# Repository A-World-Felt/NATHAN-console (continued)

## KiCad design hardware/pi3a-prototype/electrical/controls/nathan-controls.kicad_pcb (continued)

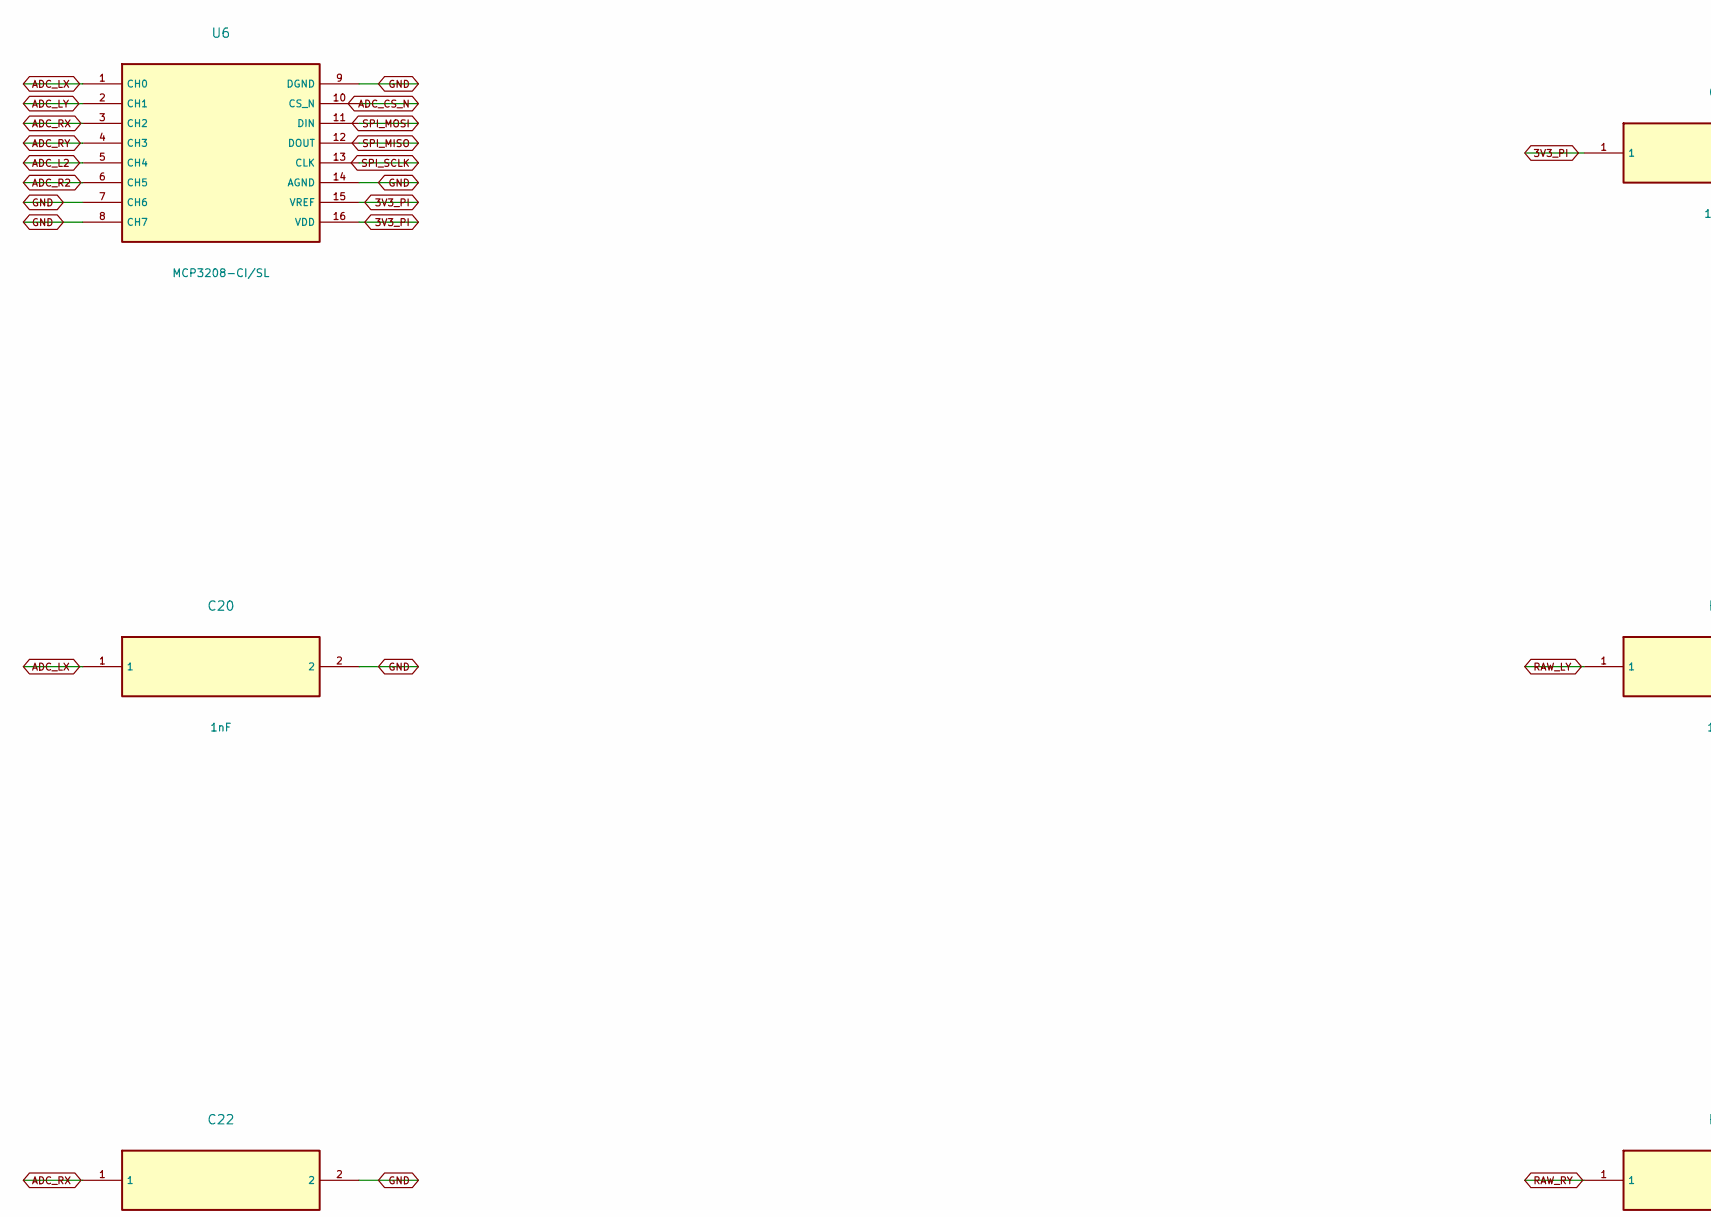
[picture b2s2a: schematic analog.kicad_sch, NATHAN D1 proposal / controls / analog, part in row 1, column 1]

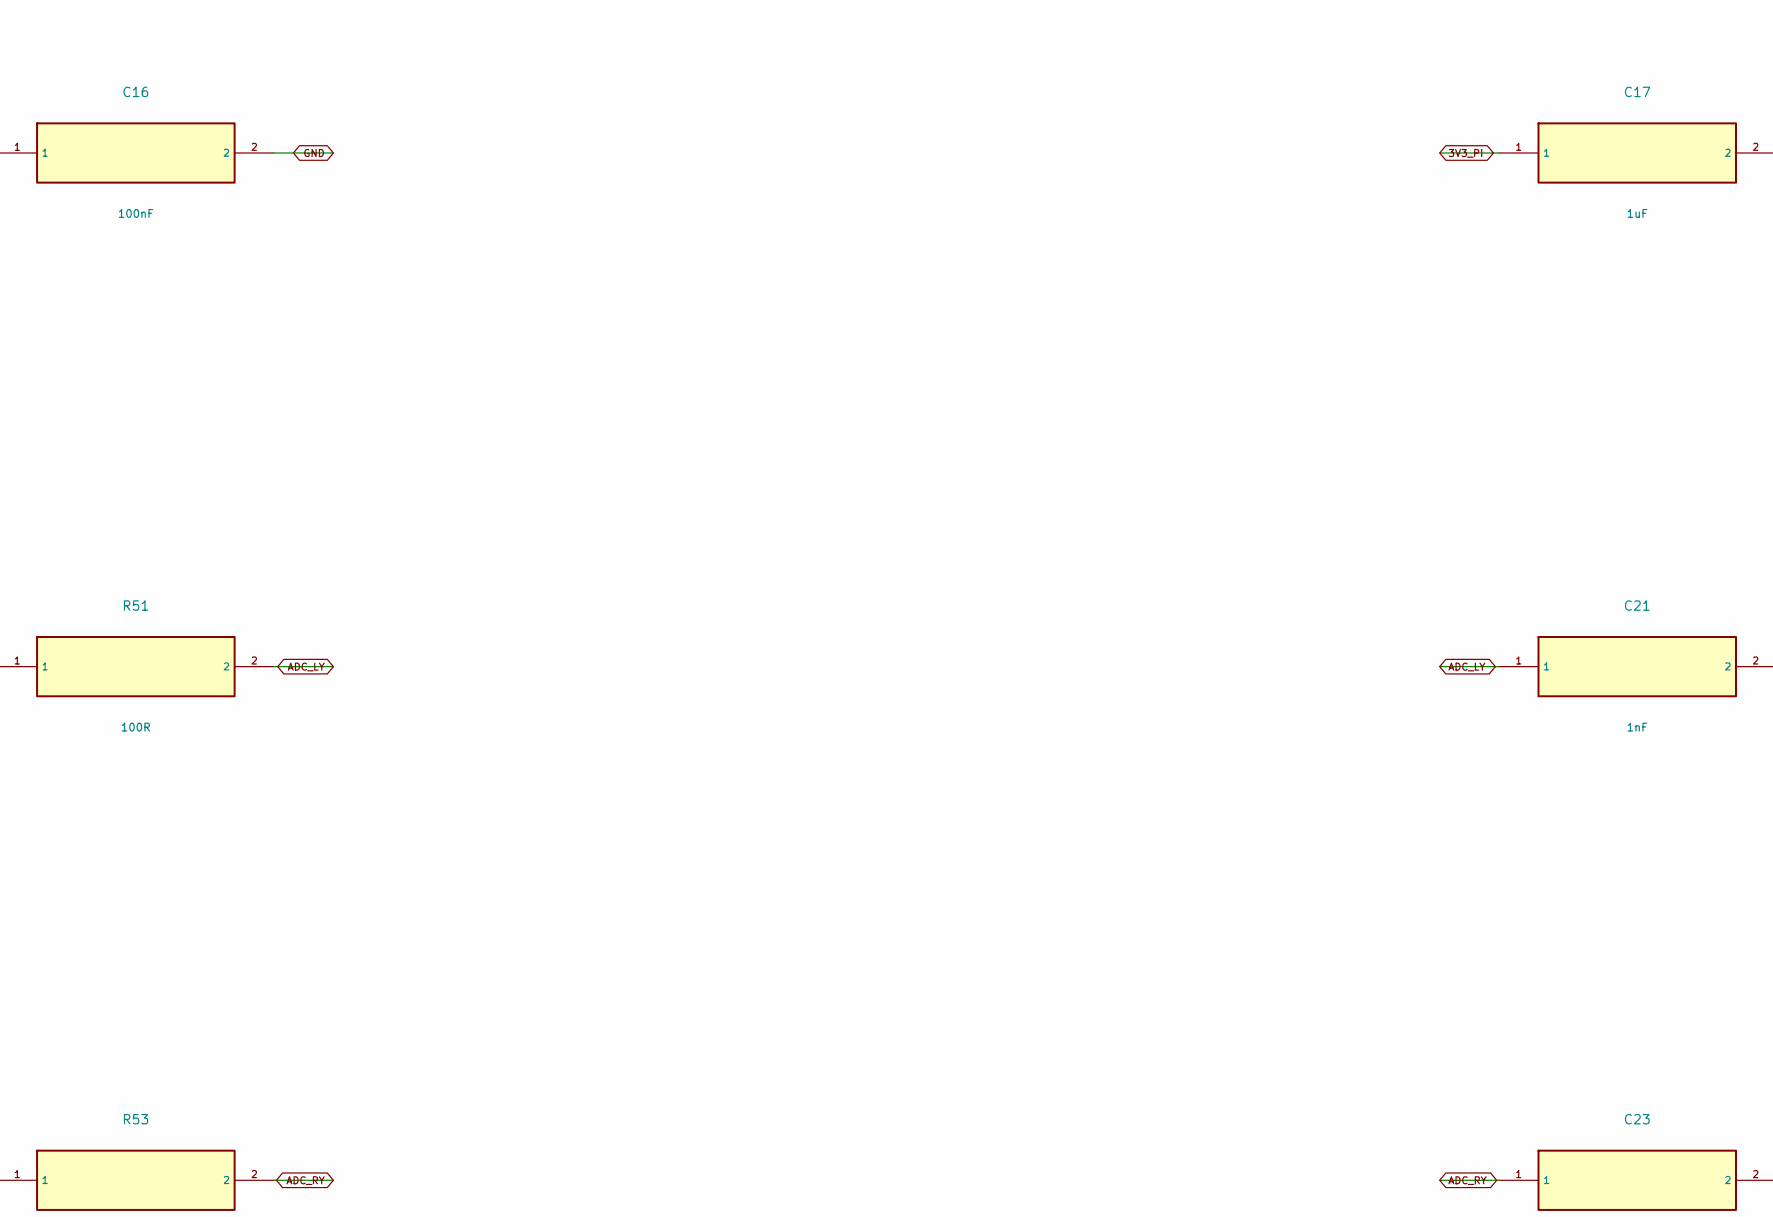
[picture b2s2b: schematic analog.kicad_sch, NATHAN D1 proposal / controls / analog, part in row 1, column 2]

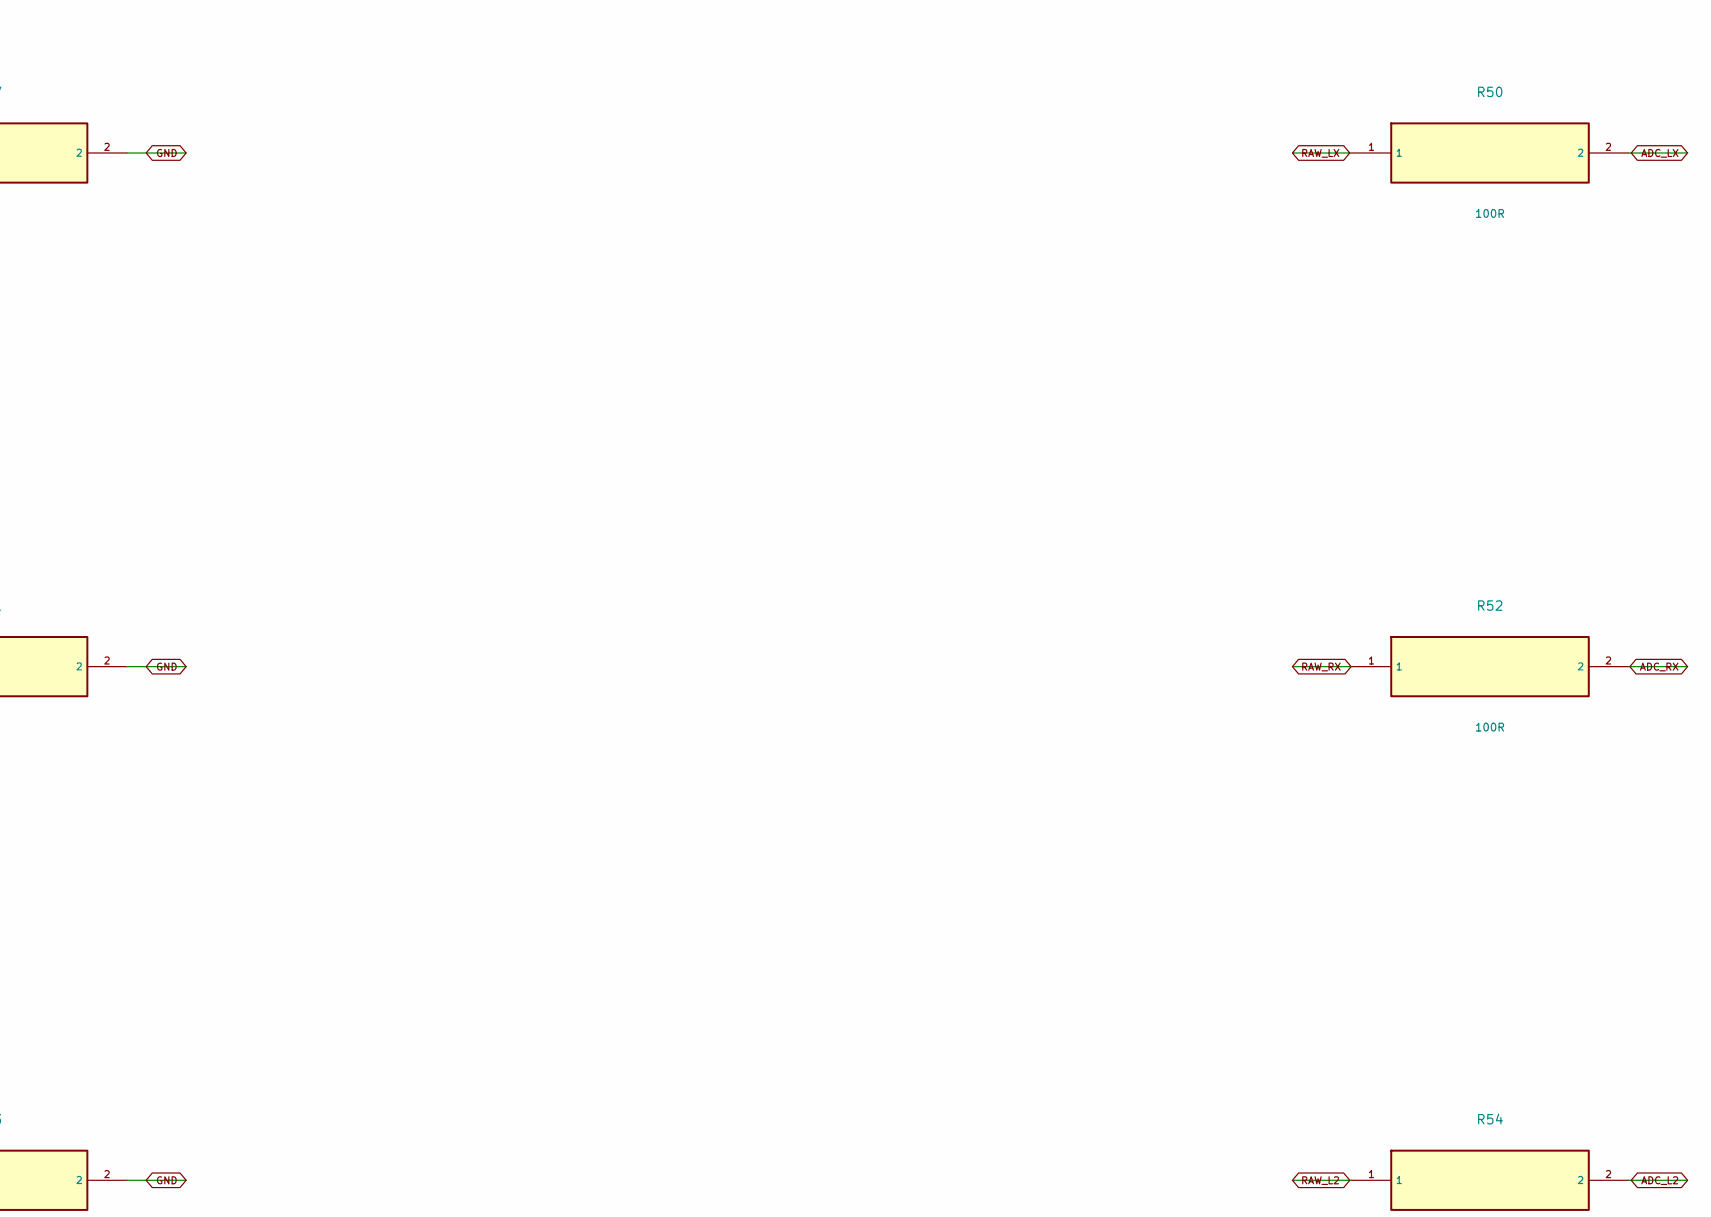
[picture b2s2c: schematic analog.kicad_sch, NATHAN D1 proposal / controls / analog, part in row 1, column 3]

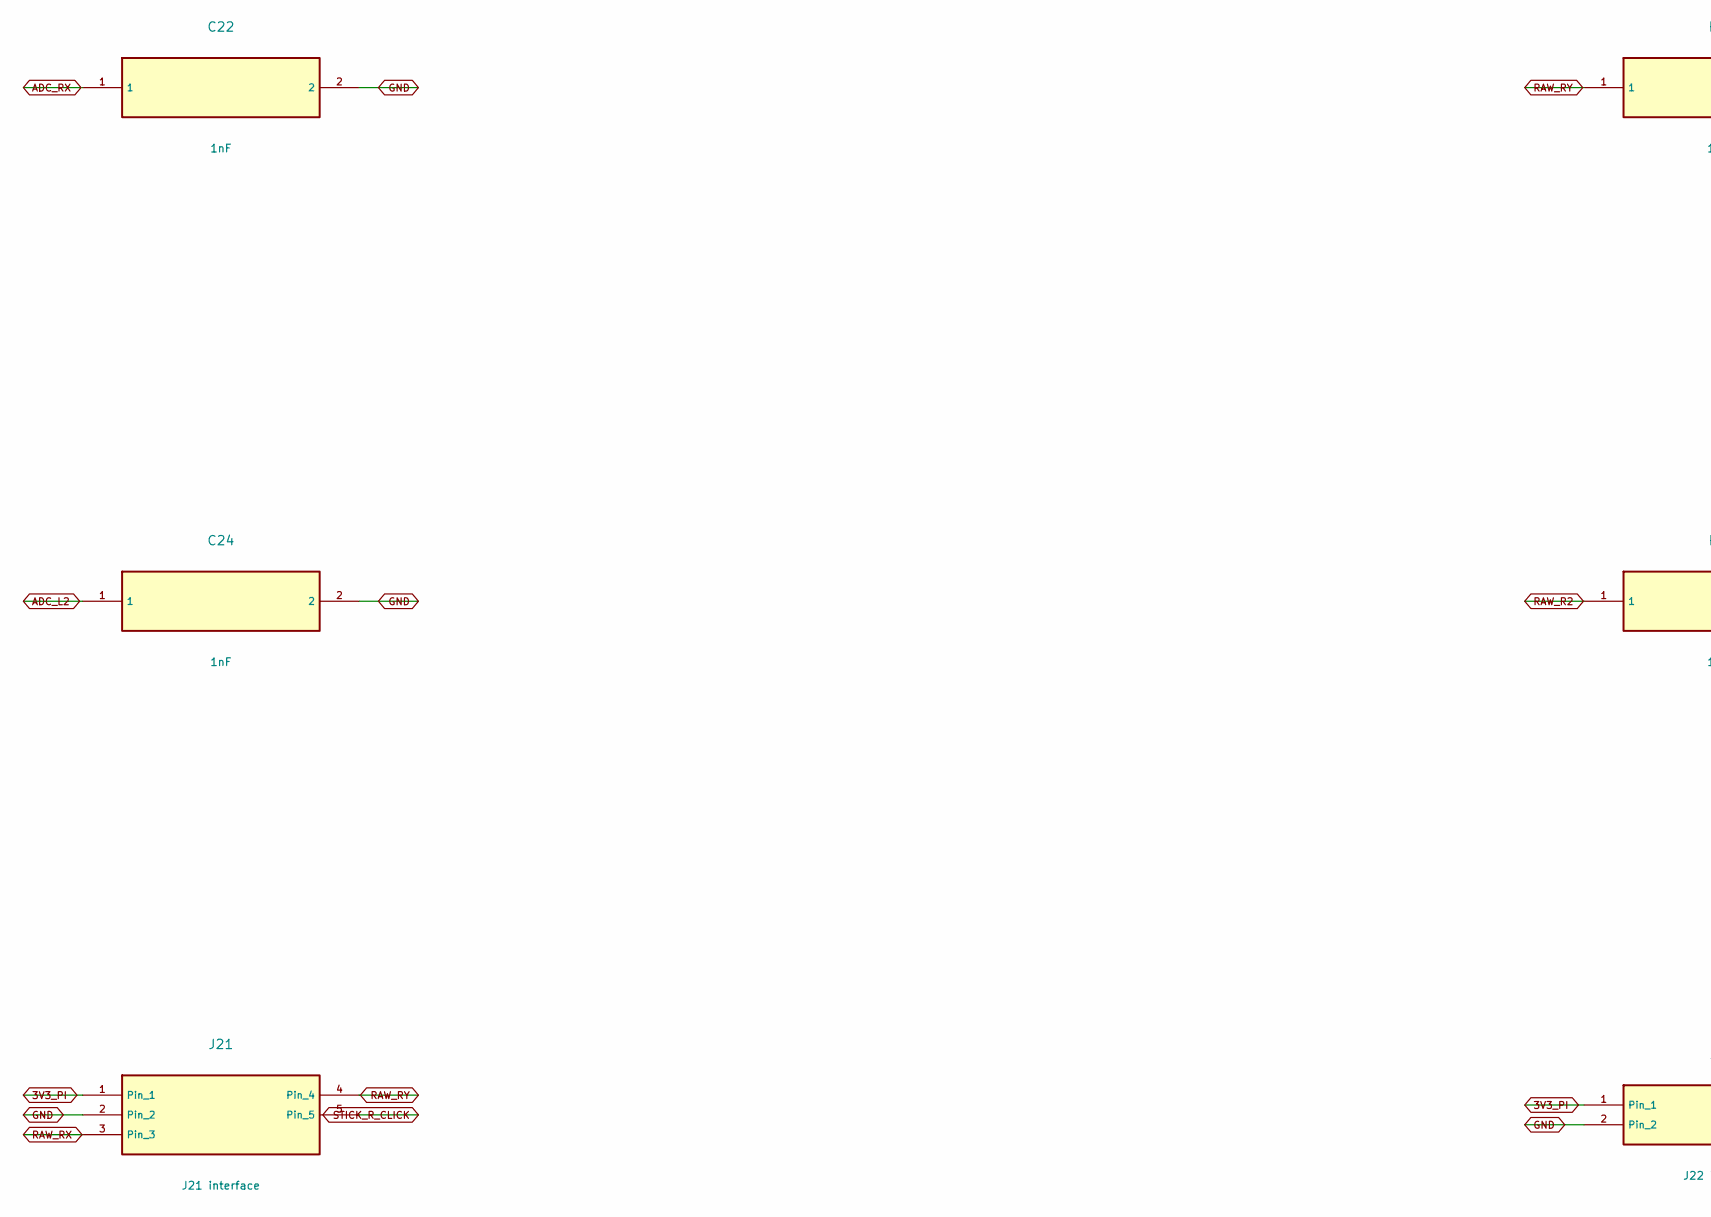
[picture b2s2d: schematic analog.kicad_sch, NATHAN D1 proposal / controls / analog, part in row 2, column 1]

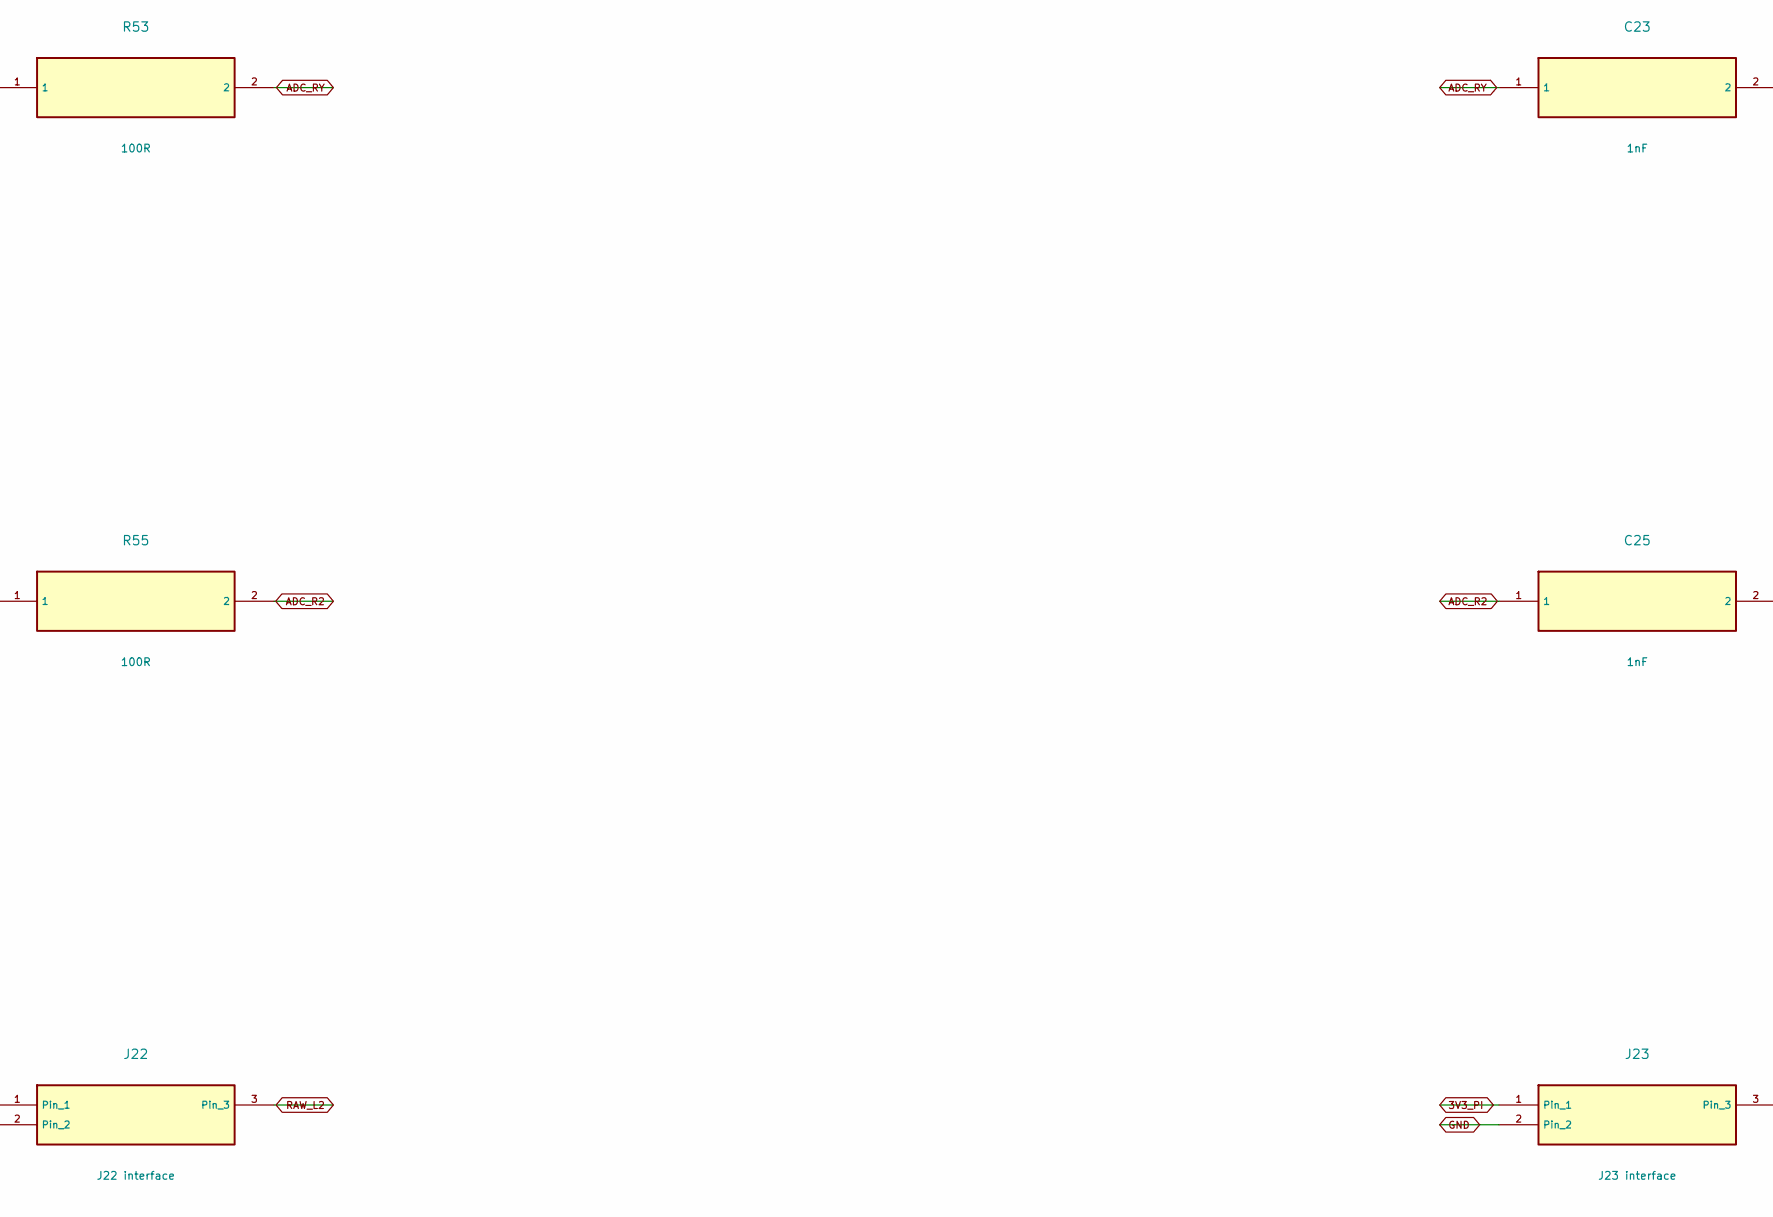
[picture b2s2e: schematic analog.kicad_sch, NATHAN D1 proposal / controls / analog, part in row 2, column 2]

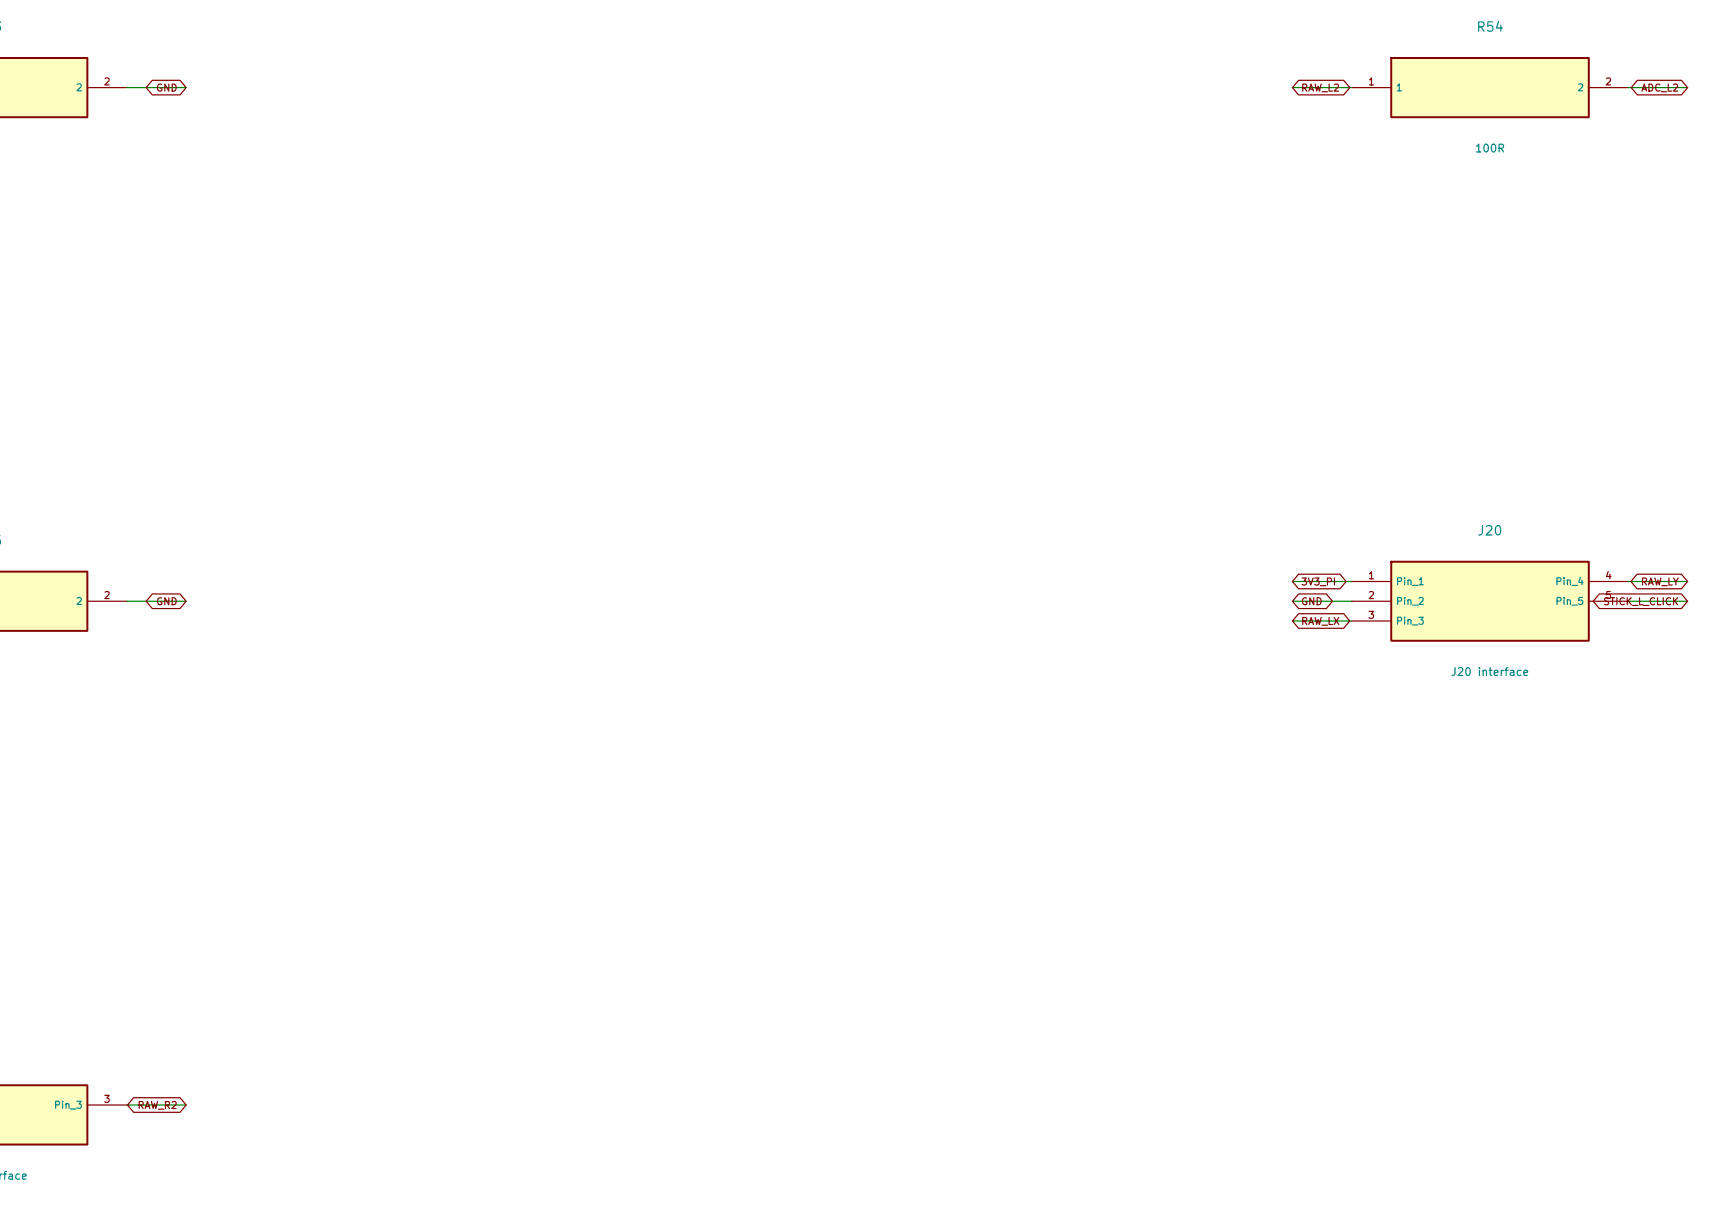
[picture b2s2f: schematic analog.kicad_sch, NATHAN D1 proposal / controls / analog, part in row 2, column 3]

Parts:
C16: 100nF; C_0603_1608Metric
C17: 1uF; C_0603_1608Metric
C20, C21, C22, C23, C24, C25: 1nF; C_0603_1608Metric
J20: J20 interface; JST_PH_B5B-PH-K_1x05_P2.00mm_Vertical
J21: J21 interface; JST_PH_B5B-PH-K_1x05_P2.00mm_Vertical
J22: J22 interface; JST_PH_B3B-PH-K_1x03_P2.00mm_Vertical
J23: J23 interface; JST_PH_B3B-PH-K_1x03_P2.00mm_Vertical
R50, R51, R52, R53, R54, R55: 100R; R_0603_1608Metric
U6: MCP3208-CI/SL; SOIC-16_3.9x9.9mm_P1.27mm

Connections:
3V3_PI: C16.1, C17.1, J20.1, J21.1, J22.1, J23.1, U6.15 (VREF), U6.16 (VDD); also elsewhere on the board
ADC_CS_N: U6.10 (CS_N); also elsewhere on the board
ADC_L2: C24.1, R54.2, U6.5 (CH4)
ADC_LX: C20.1, R50.2, U6.1 (CH0)
ADC_LY: C21.1, R51.2, U6.2 (CH1)
ADC_R2: C25.1, R55.2, U6.6 (CH5)
ADC_RX: C22.1, R52.2, U6.3 (CH2)
ADC_RY: C23.1, R53.2, U6.4 (CH3)
GND: C16.2, C17.2, C20.2, C21.2, C22.2, C23.2, C24.2, C25.2, J20.2, J21.2, J22.2, J23.2, U6.7 (CH6), U6.8 (CH7), U6.9 (DGND), U6.14 (AGND); also elsewhere on the board
RAW_L2: J22.3, R54.1
RAW_LX: J20.3, R50.1
RAW_LY: J20.4, R51.1
RAW_R2: J23.3, R55.1
RAW_RX: J21.3, R52.1
RAW_RY: J21.4, R53.1
SPI_MISO: U6.12 (DOUT); also elsewhere on the board
SPI_MOSI: U6.11 (DIN); also elsewhere on the board
SPI_SCLK: U6.13 (CLK); also elsewhere on the board
STICK_L_CLICK: J20.5; also elsewhere on the board
STICK_R_CLICK: J21.5; also elsewhere on the board

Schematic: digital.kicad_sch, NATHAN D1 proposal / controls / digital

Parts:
C15: 100nF; C_0603_1608Metric
J24: J24 interface
J25: J25 interface
R30, R31, R32, R33, R34, R35, R36, R37, R38, R39, R40, R41, R42, R43: 10k; R_0603_1608Metric
SW2, SW3, SW4, SW5, SW6, SW7, SW8, SW9, SW10, SW11: B3F-4055 candidate; SW_PUSH-12mm
U7: MCP23017-E/SO; SOIC-28W_7.5x17.9mm_P1.27mm

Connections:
3V3_PI: C15.1, R30.2, R31.2, R32.2, R33.2, R34.2, R35.2, R36.2, R37.2, R38.2, R39.2, R40.2, R41.2, R42.2, R43.2, U7.9 (VDD); also elsewhere on the board
CENTRAL_1: R38.1, SW10.1 (contact_1), U7.2 (GPB1)
CENTRAL_2: R39.1, SW11.1 (contact_1), U7.3 (GPB2)
CTRL_RESET_N: U7.18 (RESET_N); also elsewhere on the board
FACE_L_DOWN: R32.1, SW4.1 (contact_1), U7.23 (GPA2)
FACE_L_LEFT: R33.1, SW5.1 (contact_1), U7.24 (GPA3)
FACE_L_RIGHT: R31.1, SW3.1 (contact_1), U7.22 (GPA1)
FACE_L_UP: R30.1, SW2.1 (contact_1), U7.21 (GPA0)
FACE_R_DOWN: R36.1, SW8.1 (contact_1), U7.27 (GPA6)
FACE_R_LEFT: R37.1, SW9.1 (contact_1), U7.1 (GPB0)
FACE_R_RIGHT: R35.1, SW7.1 (contact_1), U7.26 (GPA5)
FACE_R_UP: R34.1, SW6.1 (contact_1), U7.25 (GPA4)
GND: C15.2, J24.2, J25.2, SW2.2 (contact_2), SW3.2 (contact_2), SW4.2 (contact_2), SW5.2 (contact_2), SW6.2 (contact_2), SW7.2 (contact_2), SW8.2 (contact_2), SW9.2 (contact_2), SW10.2 (contact_2), SW11.2 (contact_2), U7.10 (VSS), U7.15 (A0), U7.16 (A1), U7.17 (A2); also elsewhere on the board
I2C_SCL: U7.12 (SCL); also elsewhere on the board
I2C_SDA: U7.13 (SDA); also elsewhere on the board
INPUT_IRQ_N: U7.20 (INTA); also elsewhere on the board
SHOULDER_L1: J24.1, R42.1, U7.6 (GPB5)
SHOULDER_R1: J25.1, R43.1, U7.7 (GPB6)
STICK_L_CLICK: R40.1, U7.4 (GPB3); also elsewhere on the board
STICK_R_CLICK: R41.1, U7.5 (GPB4); also elsewhere on the board

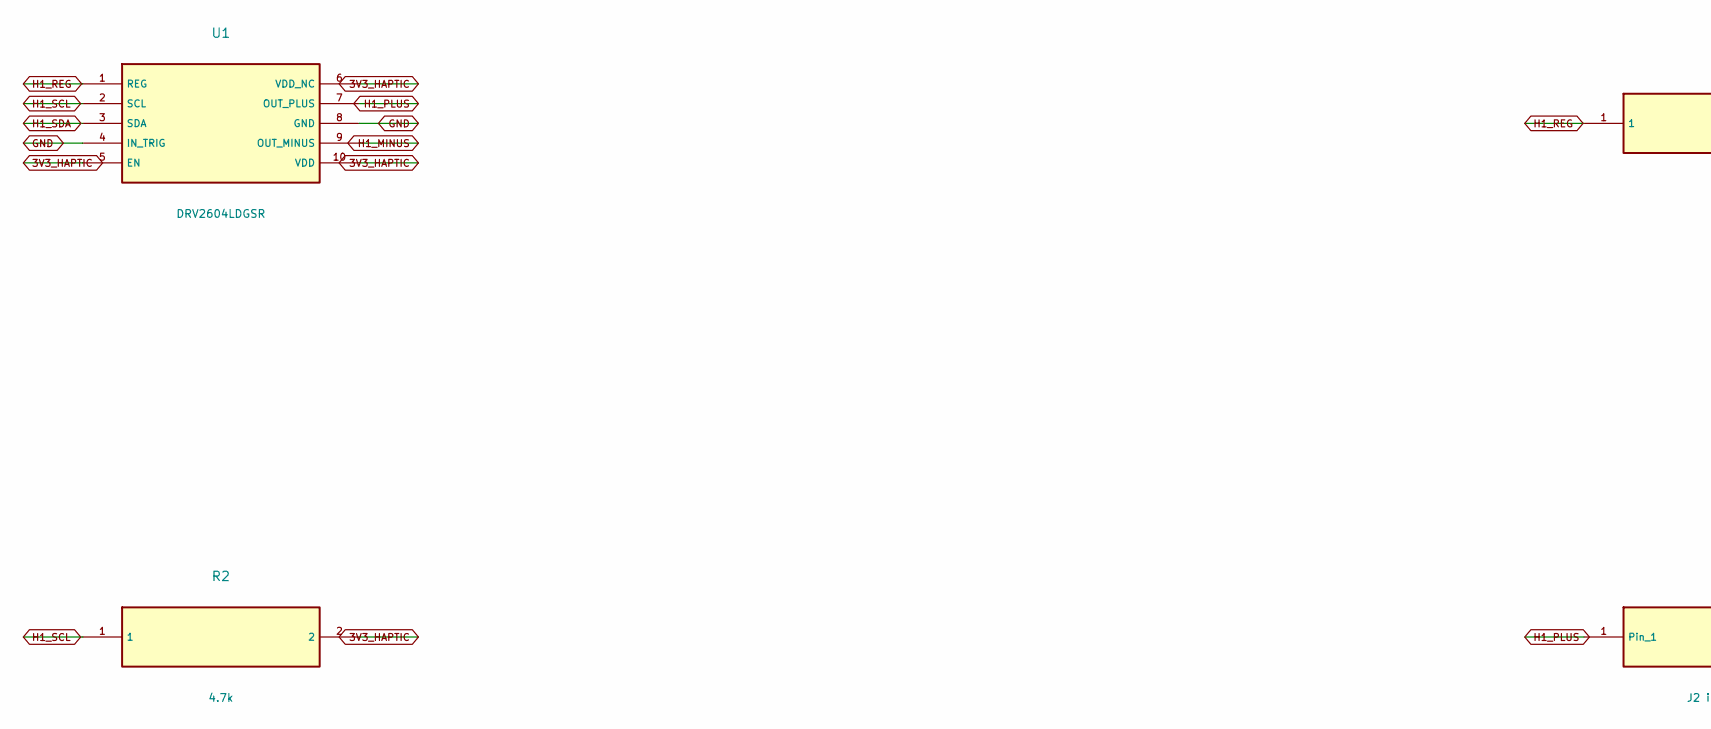
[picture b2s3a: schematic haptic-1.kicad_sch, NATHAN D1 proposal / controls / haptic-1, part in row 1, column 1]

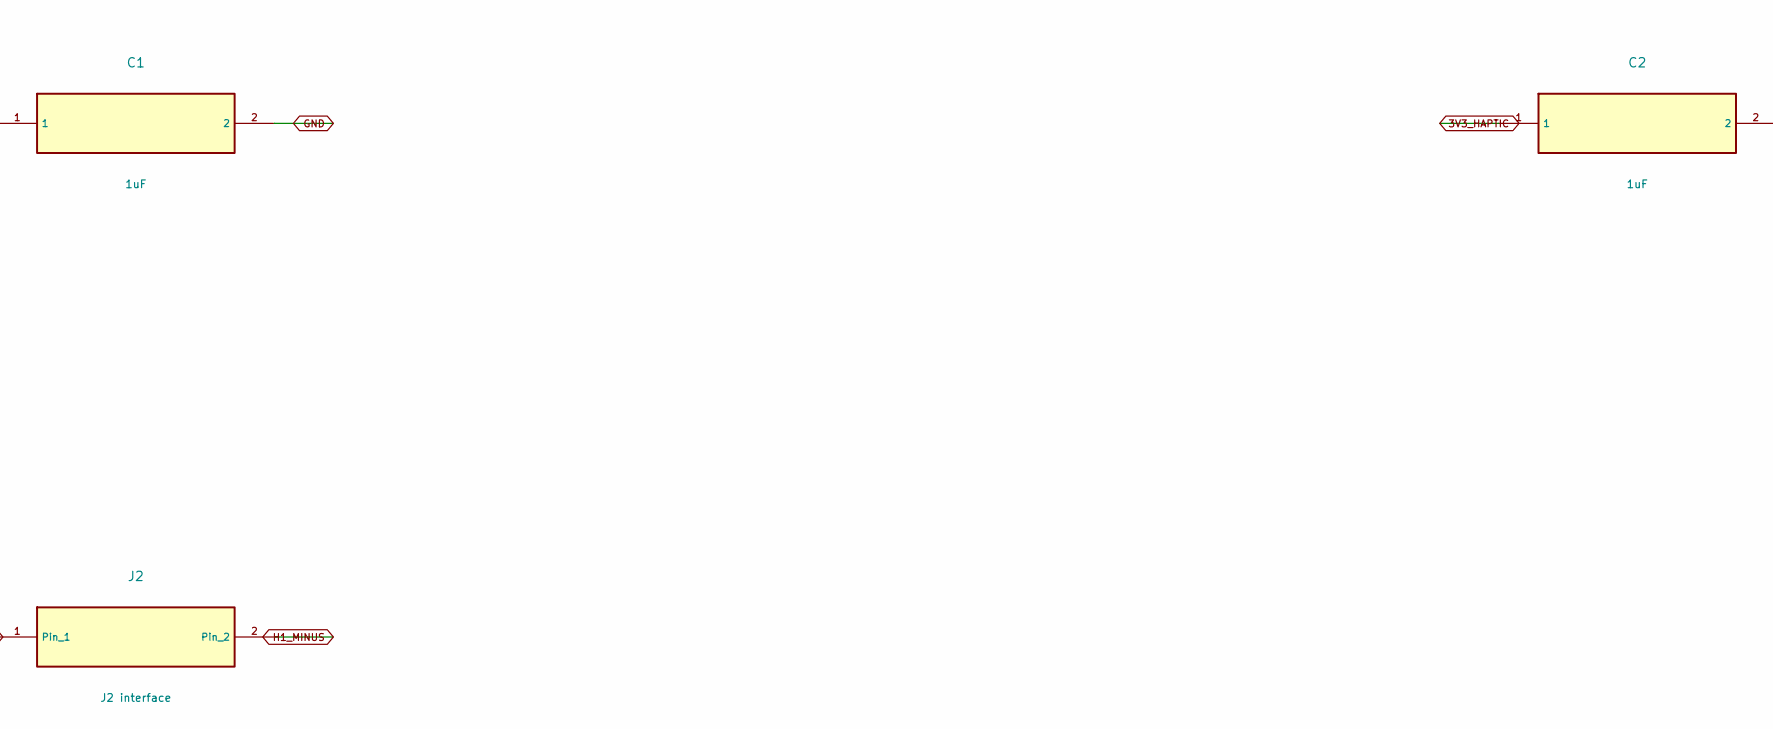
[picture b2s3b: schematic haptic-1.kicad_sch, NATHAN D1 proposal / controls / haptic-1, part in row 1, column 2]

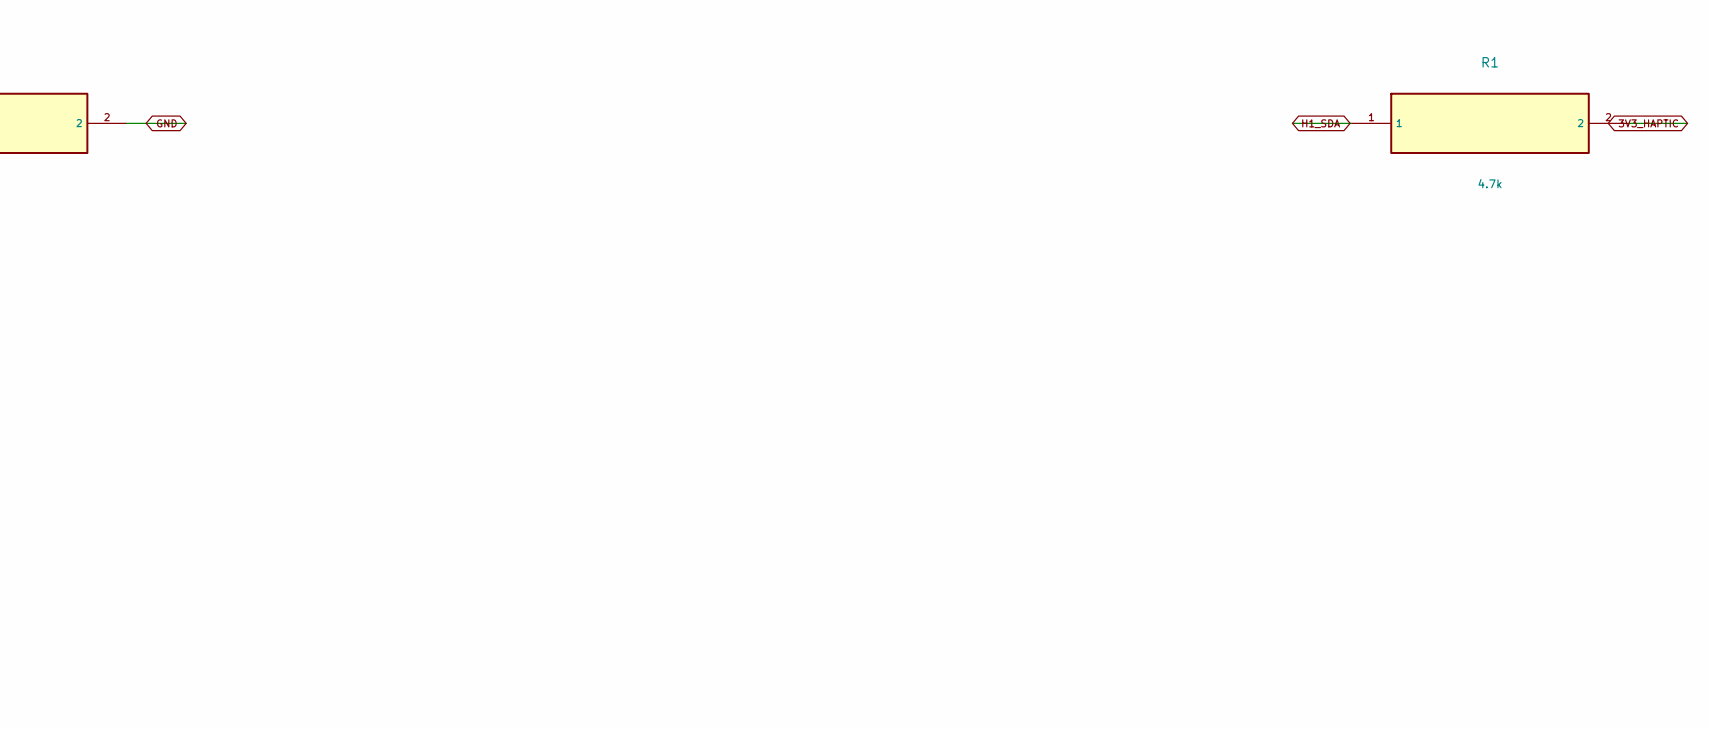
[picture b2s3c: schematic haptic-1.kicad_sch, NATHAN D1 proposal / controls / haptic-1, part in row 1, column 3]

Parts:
C1, C2: 1uF; C_0603_1608Metric
J2: J2 interface
R1, R2: 4.7k; R_0603_1608Metric
U1: DRV2604LDGSR; VSSOP-10_3x3mm_P0.5mm

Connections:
3V3_HAPTIC: C2.1, R1.2, R2.2, U1.5 (EN), U1.6 (VDD_NC), U1.10 (VDD); also elsewhere on the board
GND: C1.2, C2.2, U1.4 (IN_TRIG), U1.8 (GND); also elsewhere on the board
H1_MINUS: J2.2, U1.9 (OUT_MINUS)
H1_PLUS: J2.1, U1.7 (OUT_PLUS)
H1_REG: C1.1, U1.1 (REG)
H1_SCL: R2.1, U1.2 (SCL); also elsewhere on the board
H1_SDA: R1.1, U1.3 (SDA); also elsewhere on the board
